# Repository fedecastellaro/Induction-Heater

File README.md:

# **INDUCTION HEATER**

Circuito básico para el trabajo práctico obligatorio de la materia ELECTRONICA DE POTENCIA de 5to año UTN FRBA.

Hecho en KiCad

# Estado del PCB:
	- TERMINADO.

# Observaciones:

	- "TPO_Potencia_V1": PCB con los transistores en bottom layer y en sentido horizontal, utilizando el cobre de la placa como disipador + punto 				     de contacto.
	- "TPO_Potencia_V2": PCB con los transistores en top layer y de manera verticual

	- Revisar el routeado del PIN 6 del integrado.
	- Para el puente de diodos de baja potencia se utilizó el DB153 (stock en ELEMON). Posible reemplazarlo por cualquier puente
	  genérico con un encapsulado DIP-4
	- En caso de tener un transformador para la parte de alimentación, se debe conectar en las borneras de "Entrada 220V" y "Salida Alt 12v"
	- La bornera "Entrada 220" tiene 220V alterna, TENER CUIDADO!!

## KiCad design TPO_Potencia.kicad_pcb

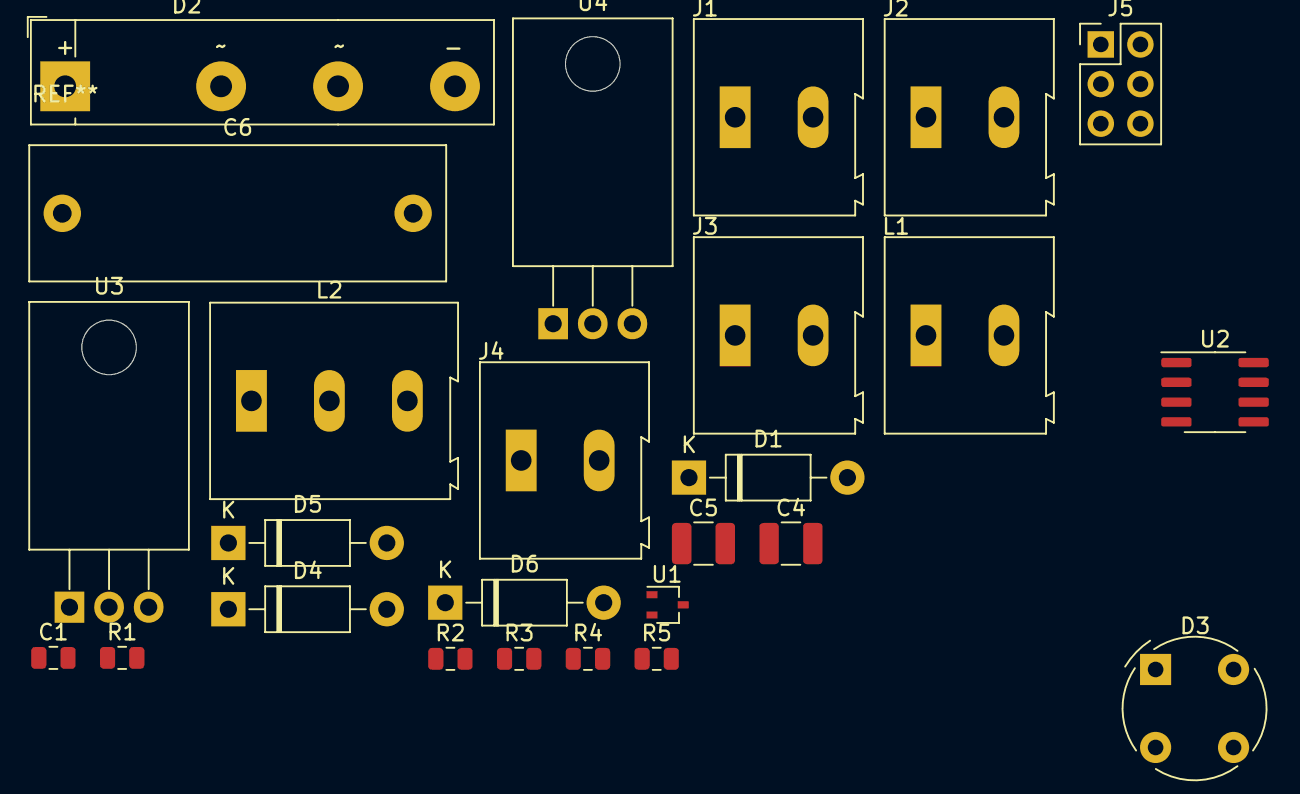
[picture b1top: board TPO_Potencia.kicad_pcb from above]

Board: 2 copper layers, 26 parts (0 on the bottom side), 21 nets, no tracks yet.

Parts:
C1: 2.2nF; C_0805_2012Metric
C4: 47nF; C_1210_3225Metric
C5: 47pF; C_1210_3225Metric
C6: 220nF; C_Rect_L26.5mm_W8.5mm_P22.50mm_MKS4
D1: 1N4738(8,2v); D_DO-41_SOD81_P10.16mm_Horizontal
D2: RBV3500; RBV25
D3: RBV3500; Diode_Bridge_Round_D9.0mm
D4: BA159; D_DO-41_SOD81_P10.16mm_Horizontal
D5, D6: 1N4742A; D_DO-41_SOD81_P10.16mm_Horizontal
J1: Entrada_Alterna; TerminalBlock_Altech_AK300-2_P5.00mm
J2: Entrada 220V Trafo; TerminalBlock_Altech_AK300-2_P5.00mm
J3: Salida 12V alt; TerminalBlock_Altech_AK300-2_P5.00mm
J4: Entrada_DC; TerminalBlock_Altech_AK300-2_P5.00mm
J5: Conn_02x03_Odd_Even; PinHeader_2x03_P2.54mm_Vertical
L1: INDUCTOR; TerminalBlock_Altech_AK300-2_P5.00mm
L2: INDUCTOR; TerminalBlock_Altech_AK300-3_P5.00mm
R1: 220; R_0805_2012Metric
R2: 10k; R_0805_2012Metric
R3: 1k; R_0805_2012Metric
R4, R5: 120; R_0805_2012Metric
U1: SSM3K16FU; SOT-323_SC-70
U2: IR2153; SOIC-8_3.9x4.9mm_P1.27mm
U3, U4: STP12N50M2; TO-220-3_Horizontal_TabDown

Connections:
/V1_alt_12V: D3.3, J3.2
/V2_alt_12V: D3.2, J3.1
/V_DC_Pulsante: C4.1, D2.1, U3.2
GND: C1.2, C5.2, D1.2, D2.4, D3.4, D6.2, J4.1, R2.1, U1.2, U2.4, U4.3
unnamed: C1.1, U1.3, U2.3
unnamed: D3.1, J5.5
unnamed: C6.1, D5.2, U2.6, U3.3, U4.2
unnamed: C4.2, C5.1, L2.2
unnamed: C6.2, L1.1
unnamed: D1.1, R1.1
unnamed: D2.2, J1.1, J2.1
unnamed: D2.3, J1.2, J2.2
unnamed: D5.1, R4.1, U3.1
unnamed: D6.1, R5.1, U4.1
unnamed: J4.2, J5.1
unnamed: L1.2, L2.1
unnamed: R1.2, R2.2, U1.1
unnamed: R3.1, U2.2
unnamed: R4.2, U2.7
unnamed: R5.2, U2.5
VCC: D4.2, J5.2, J5.4, J5.6, U2.1

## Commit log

2020-08-12 test
2020-08-12 SCH BÁSICO
2020-08-12 Readme
2020-08-12 Esquematico terminado, falta asignar footprints correspondientes
2020-08-12 Actualizo tareas a hacer
2020-08-12 Agrego varios footprints, los que faltan los aclaro en el ReadMe
2020-08-13 IR2153 corregido
2020-09-14 PCB terminado
2020-09-14 README info update
